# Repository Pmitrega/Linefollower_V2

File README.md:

# Linefollower_V2
Continuation of Linefollower project on new board

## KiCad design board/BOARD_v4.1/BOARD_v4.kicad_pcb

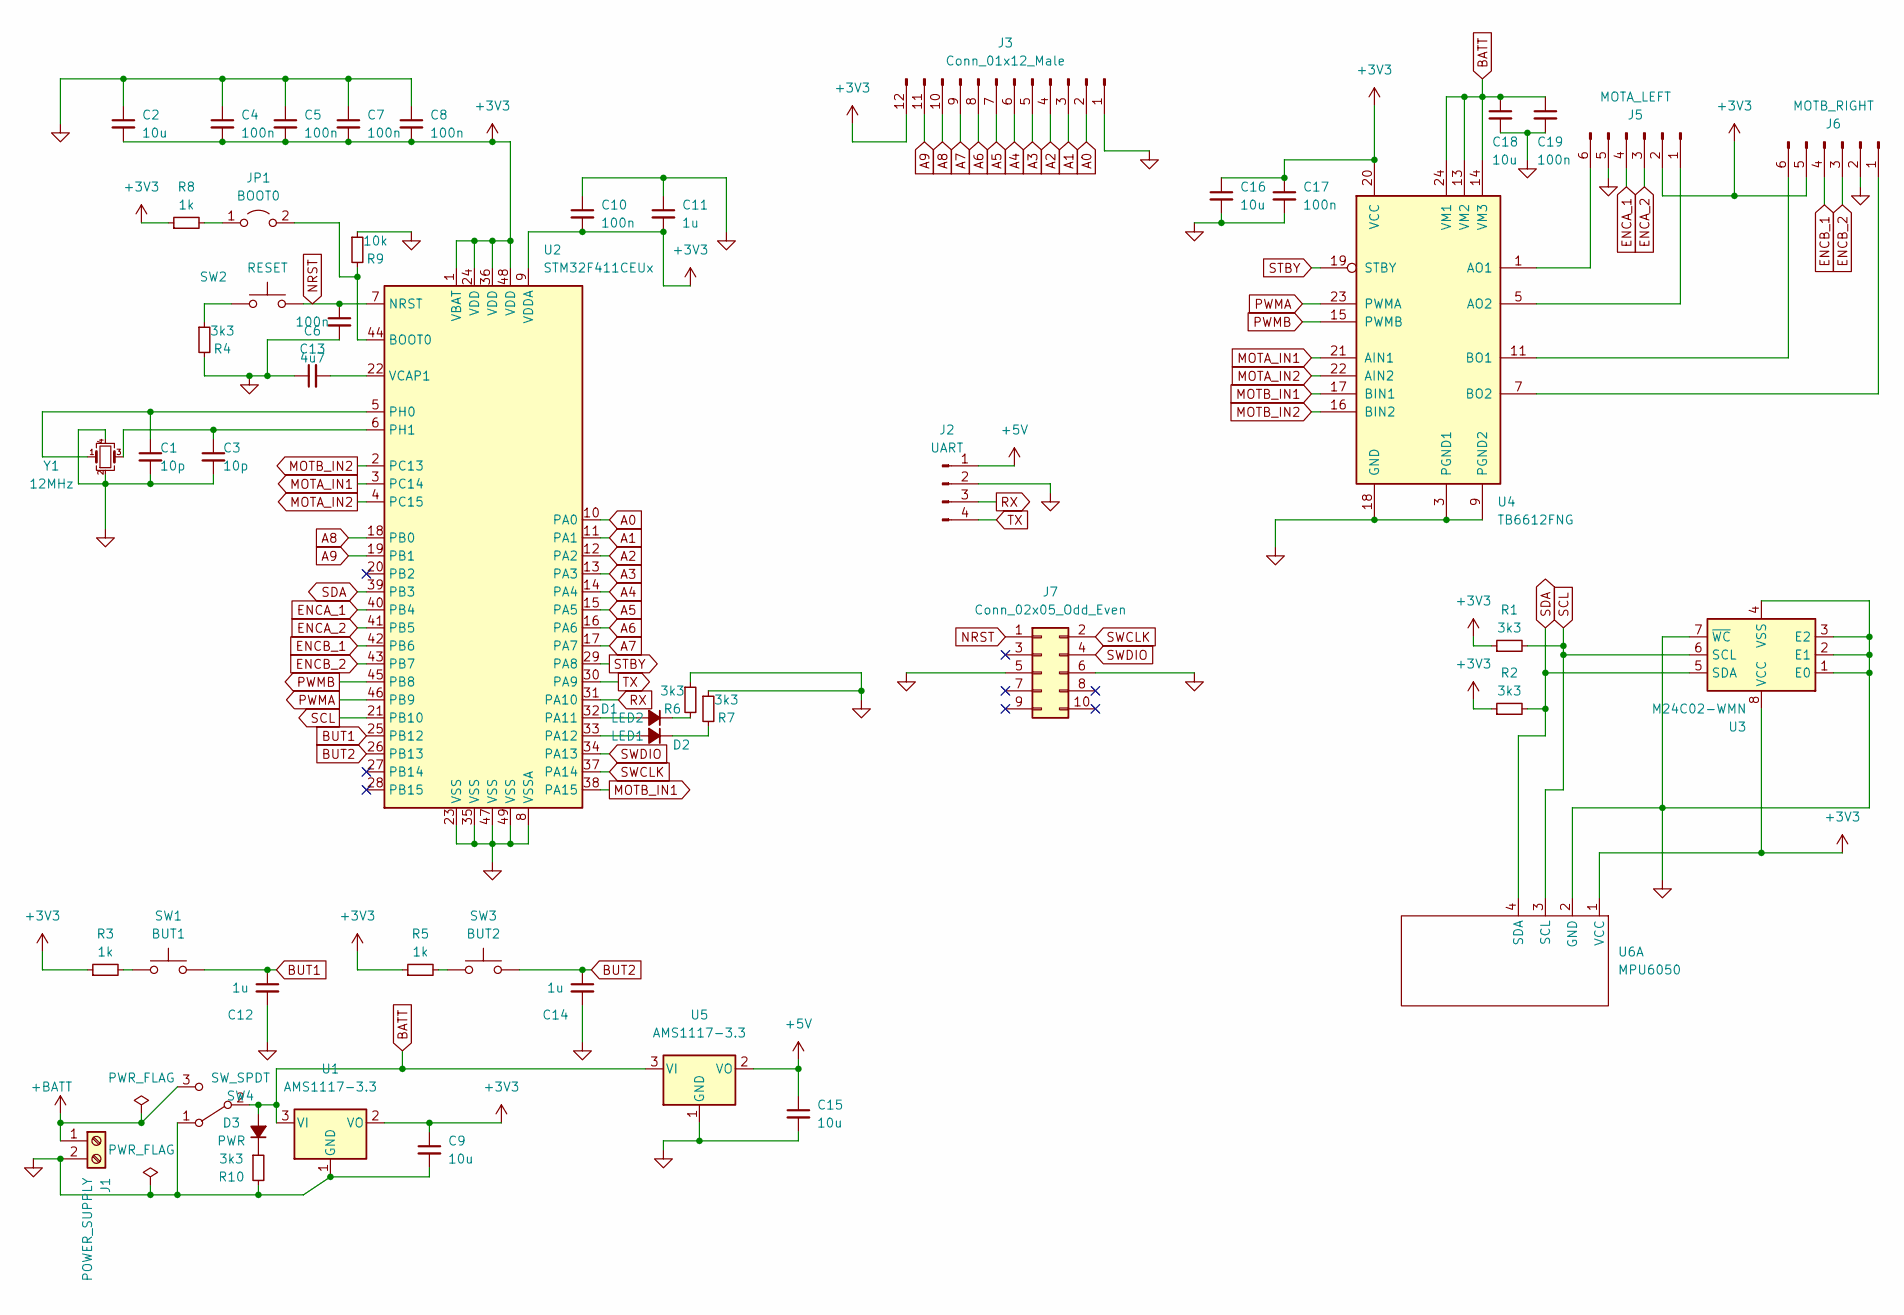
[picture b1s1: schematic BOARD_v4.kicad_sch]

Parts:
C1, C3: 10p; C_0603_1608Metric_Pad1.08x0.95mm_HandSolder
C2, C9, C15, C16, C18: 10u; C_0805_2012Metric_Pad1.18x1.45mm_HandSolder
C4, C5, C7, C8, C10, C13, C17, C19: 100n; C_0603_1608Metric_Pad1.08x0.95mm_HandSolder
C6: 4u7; C_0603_1608Metric_Pad1.08x0.95mm_HandSolder
C11, C12, C14: 1u; C_0603_1608Metric_Pad1.08x0.95mm_HandSolder
D1: LED2; LED_0805_2012Metric_Pad1.15x1.40mm_HandSolder
D2: LED1; LED_0805_2012Metric_Pad1.15x1.40mm_HandSolder
D3: PWR; LED_0805_2012Metric_Pad1.15x1.40mm_HandSolder
J1: POWER_SUPPLY; TerminalBlock_4Ucon_1x02_P3.50mm_Horizontal
J2: UART; PinSocket_1x04_P2.54mm_Vertical
J3: Conn_01x12_Male; Hirose_FH12-12S-0.5SH_1x12-1MP_P0.50mm_Horizontal
J5: MOTA_LEFT; PinSocket_1x06_P2.54mm_Vertical
J6: MOTB_RIGHT; PinSocket_1x06_P2.54mm_Vertical
J7: Conn_02x05_Odd_Even; IDC-Header_2x05_P2.54mm_Vertical
JP1: BOOT0; PinSocket_1x02_P2.54mm_Vertical
R1, R2, R4, R6, R7, R10: 3k3; R_0805_2012Metric_Pad1.20x1.40mm_HandSolder
R3, R5, R8: 1k; R_0805_2012Metric_Pad1.20x1.40mm_HandSolder
R9: 10k; R_0805_2012Metric_Pad1.20x1.40mm_HandSolder
SW1: BUT1; SW_PUSH_6mm
SW2: RESET; SW_PUSH_6mm
SW3: BUT2; SW_PUSH_6mm
SW4: SW_SPDT; SS22T20
U1, U5: AMS1117-3.3; SOT-223-3_TabPin2
U2: STM32F411CEUx; QFN-48-1EP_7x7mm_P0.5mm_EP5.6x5.6mm; LCSC C60420
U3: M24C02-WMN; SOIC-8_3.9x4.9mm_P1.27mm
U4: TB6612FNG; SSOP-24_5.3x8.2mm_P0.65mm; LCSC C88224
U6: MPU6050; MPU6050THT
Y1: 12MHz; Crystal_SMD_3225-4Pin_3.2x2.5mm_HandSoldering

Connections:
+3V3: C2.2, C4.2, C5.2, C7.2, C8.2, C9.1, C10.2, C11.2, C16.1, C17.1, J3.12, J5.2, J6.5, R1.1, R2.1, R3.1, R5.1, R8.1, U1.2 (VO), U2.1 (VBAT), U2.9 (VDDA), U2.24 (VDD), U2.36 (VDD), U2.48 (VDD), U3.8 (VCC), U4.20 (VCC), U6.1 (VCC)
+5V: C15.1, J2.1, U5.2 (VO)
+BATT: J1.1, SW4.3 (C)
A0: J3.2, U2.10 (PA0)
A1: J3.3, U2.11 (PA1)
A2: J3.4, U2.12 (PA2)
A3: J3.5, U2.13 (PA3)
A4: J3.6, U2.14 (PA4)
A5: J3.7, U2.15 (PA5)
A6: J3.8, U2.16 (PA6)
A7: J3.9, U2.17 (PA7)
A8: J3.10, U2.18 (PB0)
A9: J3.11, U2.19 (PB1)
BATT: C18.1, C19.1, D3.2 (A), SW4.2 (B), U1.3 (VI), U4.13 (VM2), U4.14 (VM3), U4.24 (VM1), U5.3 (VI)
BUT1: C12.1, SW1.2, U2.25 (PB12)
BUT2: C14.1, SW3.2, U2.26 (PB13)
ENCA_1: J5.4, U2.40 (PB4)
ENCA_2: J5.3, U2.41 (PB5)
ENCB_1: J6.4, U2.42 (PB6)
ENCB_2: J6.3, U2.43 (PB7)
GND: C1.2, C2.1, C3.2, C4.1, C5.1, C6.1, C7.1, C8.1, C9.2, C10.1, C11.1, C12.2, C13.2, C14.2, C15.2, C16.2, C17.2, C18.2, C19.2, J1.2, J2.2, J3.1, J5.5, J6.2, J7.5, J7.6, R4.2, R6.1, R7.1, R9.1, R10.2, SW4.1 (A), U1.1 (GND), U2.8 (VSSA), U2.23 (VSS), U2.35 (VSS), U2.47 (VSS), U2.49 (VSS), U3.1 (E0), U3.2 (E1), U3.3 (E2), U3.4 (VSS), U3.7 (~WC), U4.3 (PGND1), U4.4 (PGND1), U4.9 (PGND2), U4.10 (PGND2), U4.18 (GND), U5.1 (GND), U6.2 (GND), Y1.2, Y1.4
MOTA_IN1: U2.3 (PC14), U4.21 (AIN1)
MOTA_IN2: U2.4 (PC15), U4.22 (AIN2)
MOTB_IN1: U2.38 (PA15), U4.17 (BIN1)
MOTB_IN2: U2.2 (PC13), U4.16 (BIN2)
NRST: C13.1, J7.1, SW2.2, U2.7 (NRST)
unnamed: C1.1, U2.5 (PH0), Y1.1
unnamed: C3.1, U2.6 (PH1), Y1.3
unnamed: C6.2, U2.22 (VCAP1)
unnamed: D1.1 (K), R6.2
unnamed: D1.2 (A), U2.32 (PA11)
unnamed: D2.1 (K), R7.2
unnamed: D2.2 (A), U2.33 (PA12)
unnamed: D3.1 (K), R10.1
unnamed: J5.1, U4.5 (AO2), U4.6 (AO2)
unnamed: J5.6, U4.1 (AO1), U4.2 (AO1)
unnamed: J6.1, U4.7 (BO2), U4.8 (BO2)
unnamed: J6.6, U4.11 (BO1), U4.12 (BO1)
unnamed: JP1.1 (A), R8.2
unnamed: JP1.2 (B), R9.2, U2.44 (BOOT0)
unnamed: R3.2, SW1.1
unnamed: R4.1, SW2.1
unnamed: R5.2, SW3.1
PWMA: U2.46 (PB9), U4.23 (PWMA)
PWMB: U2.45 (PB8), U4.15 (PWMB)
RX: J2.3, U2.31 (PA10)
SCL: R1.2, U2.21 (PB10), U3.6 (SCL), U6.3 (SCL)
SDA: R2.2, U2.39 (PB3), U3.5 (SDA), U6.4 (SDA)
STBY: U2.29 (PA8), U4.19 (STBY)
SWCLK: J7.2, U2.37 (PA14)
SWDIO: J7.4, U2.34 (PA13)
TX: J2.4, U2.30 (PA9)

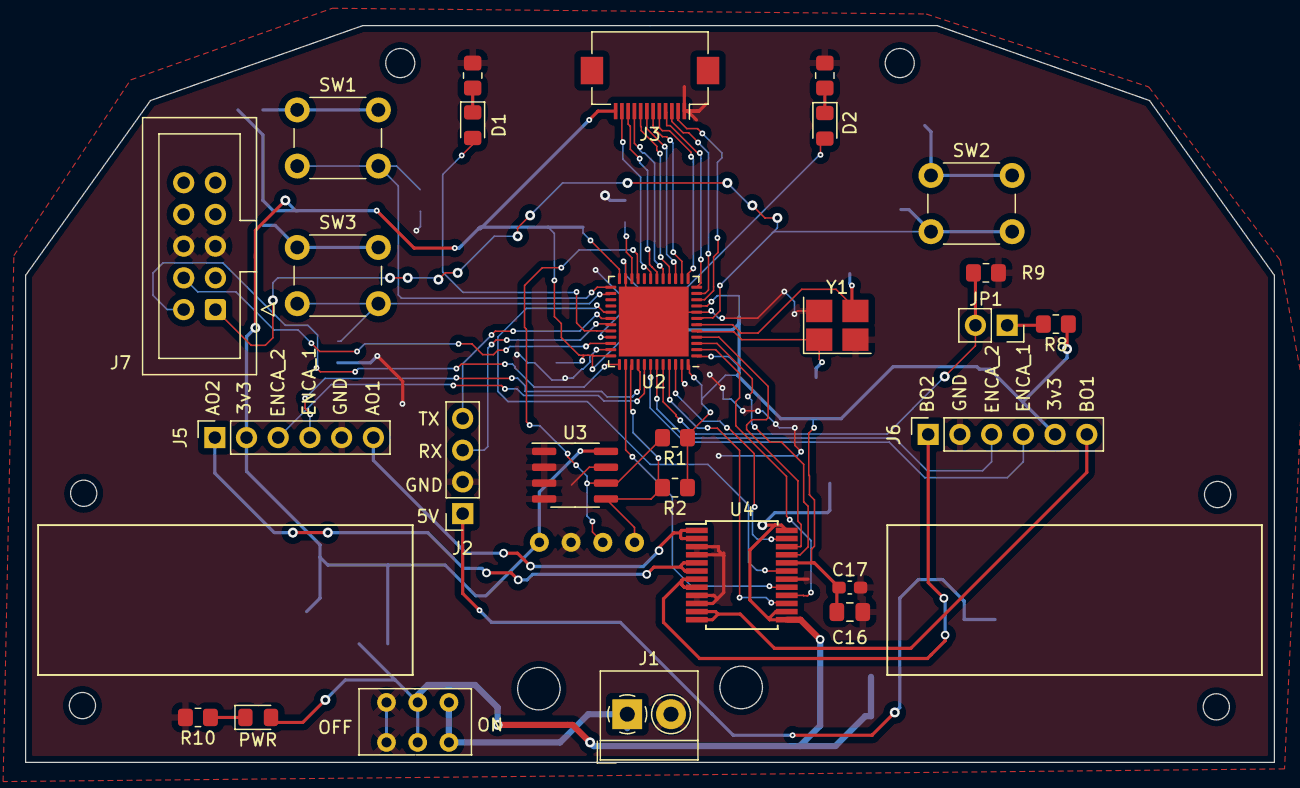
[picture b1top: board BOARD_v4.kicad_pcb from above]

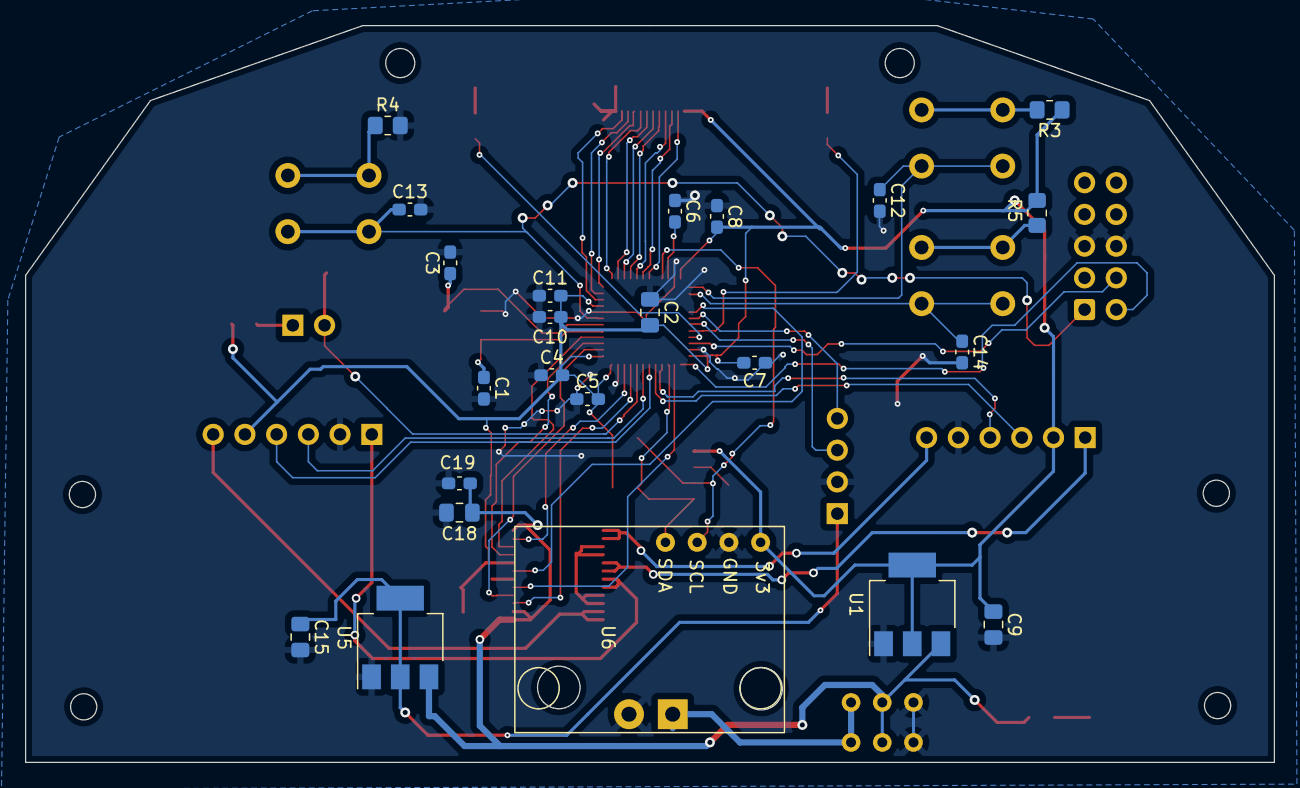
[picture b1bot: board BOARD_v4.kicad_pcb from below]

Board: 2 copper layers, 100.0 x 59.0 mm, 50 parts (23 on the bottom side), 52 nets.

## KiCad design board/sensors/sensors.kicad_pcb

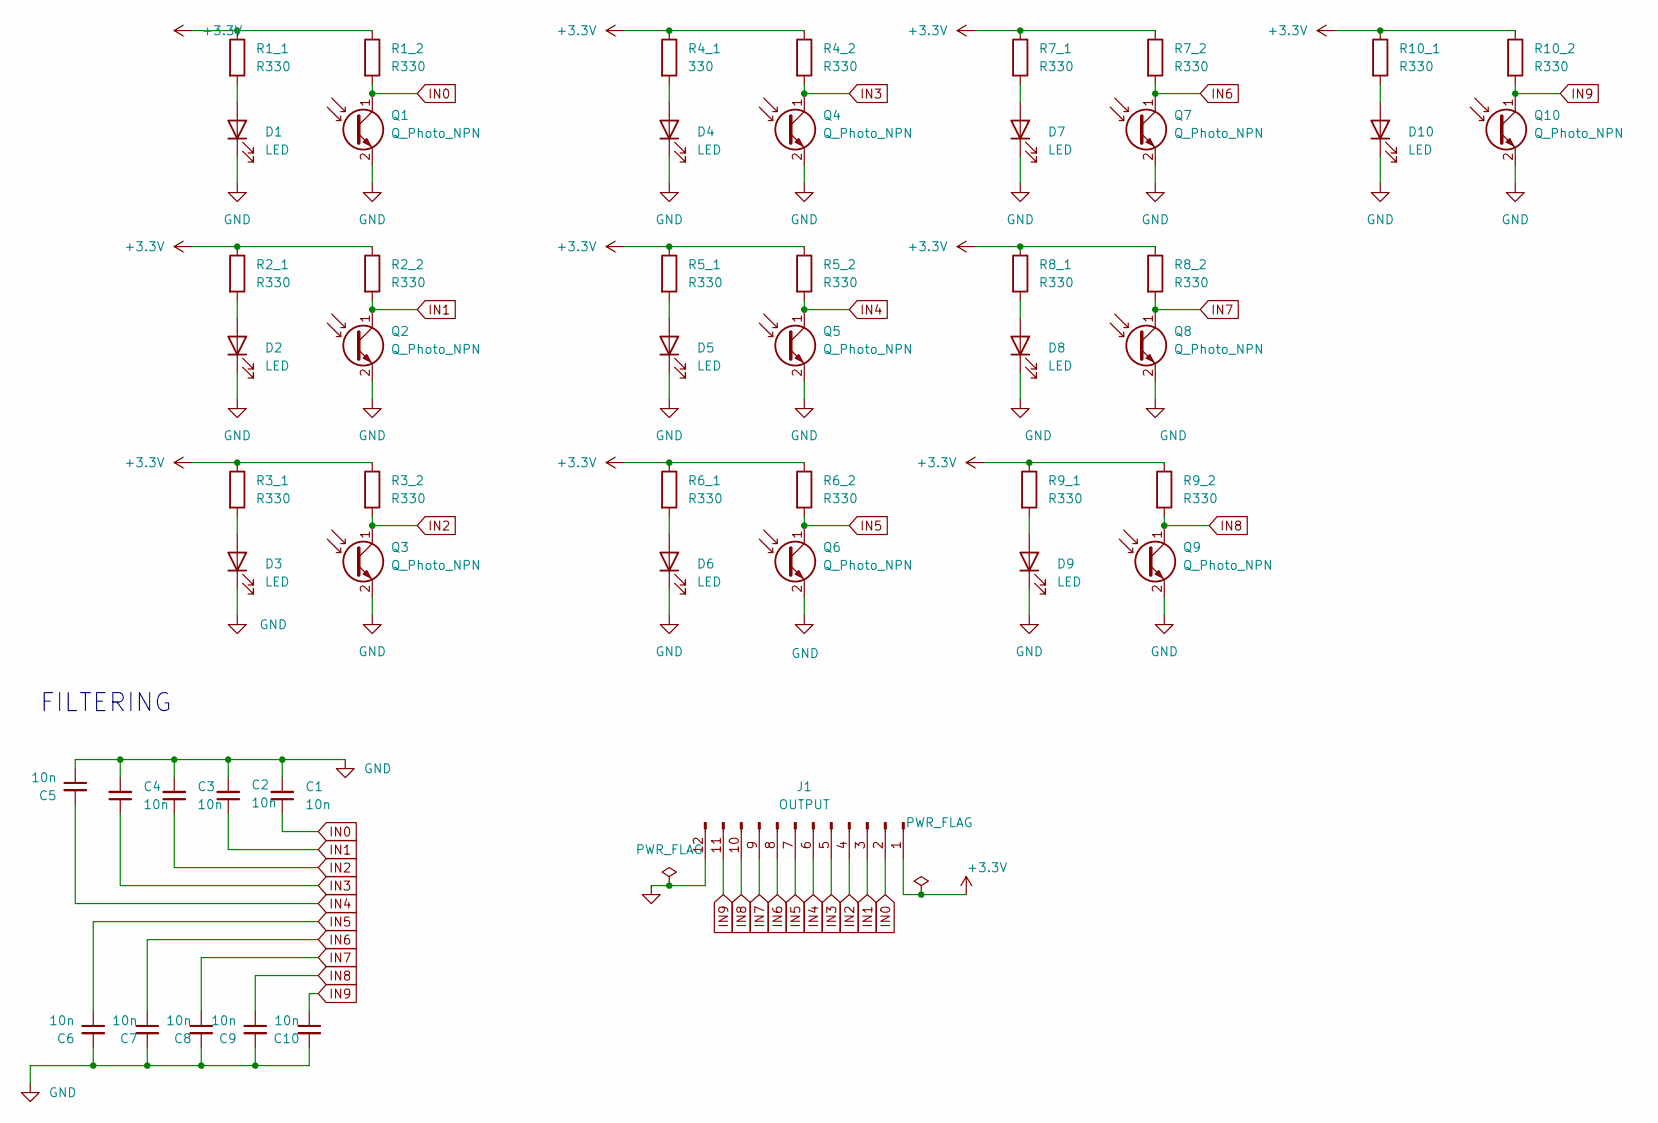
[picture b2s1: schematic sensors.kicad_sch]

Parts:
C1, C2, C3, C4, C5, C6, C7, C8, C9, C10: 10n; C_0805_2012Metric_Pad1.18x1.45mm_HandSolder
D1, D2, D3, D4, D5, D6, D7, D8, D9, D10: LED; R_0805_2012Metric_Pad1.20x1.40mm_HandSolder
J1: OUTPUT; Hirose_FH12-12S-0.5SH_1x12-1MP_P0.50mm_Horizontal
Q1, Q2, Q3, Q4, Q5, Q6, Q7, Q8, Q9, Q10: Q_Photo_NPN; LED_0805_2012Metric_Pad1.15x1.40mm_HandSolder
R1_1, R1_2, R2_1, R2_2, R3_1, R3_2, R4_2, R5_1, R5_2, R6_1, R6_2, R7_1, R7_2, R8_1, R8_2, R9_1, R9_2, R10_1, R10_2: R330; R_0805_2012Metric_Pad1.20x1.40mm_HandSolder
R4_1: 330; R_0805_2012Metric_Pad1.20x1.40mm_HandSolder

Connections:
+3.3V: J1.1, R1_1.1, R1_2.1, R2_1.1, R2_2.1, R3_1.1, R3_2.1, R4_1.1, R4_2.1, R5_1.1, R5_2.1, R6_1.1, R6_2.1, R7_1.1, R7_2.1, R8_1.1, R8_2.1, R9_1.1, R9_2.1, R10_1.1, R10_2.1
GND: C1.2, C2.2, C3.2, C4.2, C5.1, C6.2, C7.2, C8.2, C9.2, C10.2, D1.1 (K), D2.1 (K), D3.1 (K), D4.1 (K), D5.1 (K), D6.1 (K), D7.1 (K), D8.1 (K), D9.1 (K), D10.1 (K), J1.12, Q1.2 (E), Q2.2 (E), Q3.2 (E), Q4.2 (E), Q5.2 (E), Q6.2 (E), Q7.2 (E), Q8.2 (E), Q9.2 (E), Q10.2 (E)
IN0: C1.1, J1.2, Q1.1 (C), R1_2.2
IN1: C2.1, J1.3, Q2.1 (C), R2_2.2
IN2: C3.1, J1.4, Q3.1 (C), R3_2.2
IN3: C4.1, J1.5, Q4.1 (C), R4_2.2
IN4: C5.2, J1.6, Q5.1 (C), R5_2.2
IN5: C6.1, J1.7, Q6.1 (C), R6_2.2
IN6: C7.1, J1.8, Q7.1 (C), R7_2.2
IN7: C8.1, J1.9, Q8.1 (C), R8_2.2
IN8: C9.1, J1.10, Q9.1 (C), R9_2.2
IN9: C10.1, J1.11, Q10.1 (C), R10_2.2
unnamed: D1.2 (A), R1_1.2
unnamed: D2.2 (A), R2_1.2
unnamed: D3.2 (A), R3_1.2
unnamed: D4.2 (A), R4_1.2
unnamed: D5.2 (A), R5_1.2
unnamed: D6.2 (A), R6_1.2
unnamed: D7.2 (A), R7_1.2
unnamed: D8.2 (A), R8_1.2
unnamed: D9.2 (A), R9_1.2
unnamed: D10.2 (A), R10_1.2

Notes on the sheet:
FILTERING

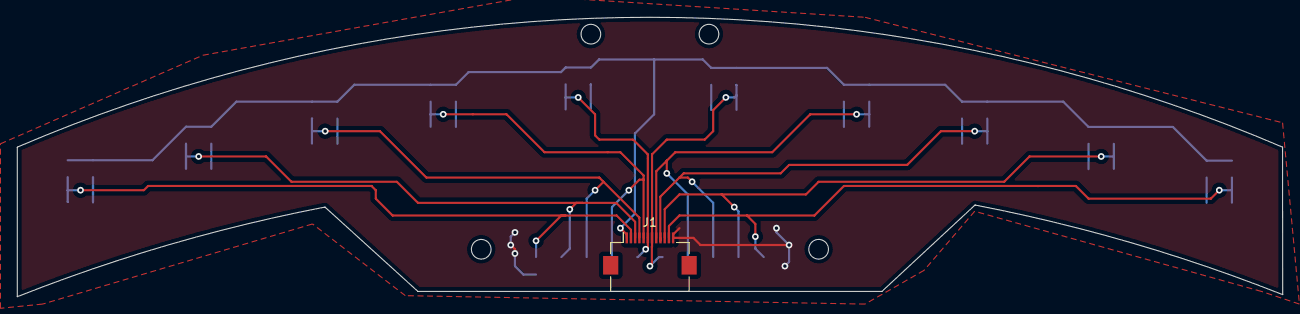
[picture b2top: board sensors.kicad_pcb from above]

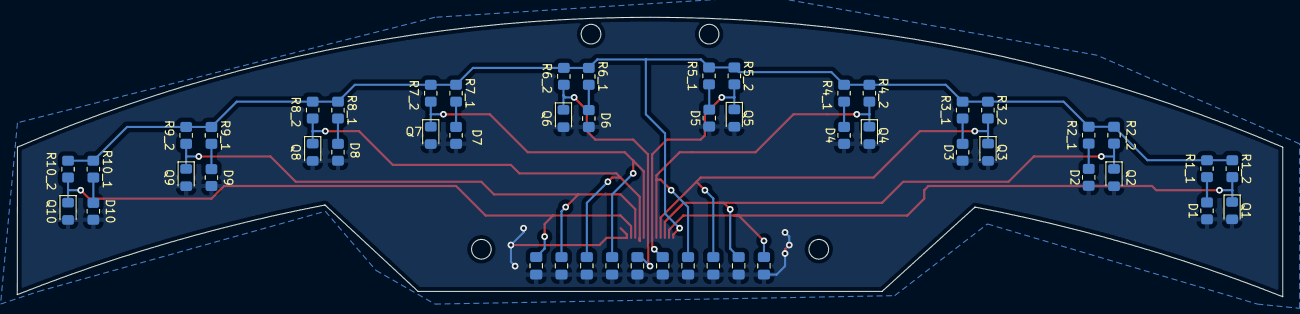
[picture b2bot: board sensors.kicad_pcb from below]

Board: 2 copper layers, 150.0 x 33.1 mm, 51 parts (50 on the bottom side), 22 nets.

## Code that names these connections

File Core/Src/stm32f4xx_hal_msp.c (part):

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    __HAL_RCC_GPIOA_CLK_ENABLE();
    __HAL_RCC_GPIOB_CLK_ENABLE();
    /**ADC1 GPIO Configuration
    PA0-WKUP     ------> ADC1_IN0
    PA1     ------> ADC1_IN1
    PA2     ------> ADC1_IN2
    PA3     ------> ADC1_IN3
    PA4     ------> ADC1_IN4
    PA5     ------> ADC1_IN5
    PA6     ------> ADC1_IN6
    PA7     ------> ADC1_IN7
    PB0     ------> ADC1_IN8
    PB1     ------> ADC1_IN9
    */
    GPIO_InitStruct.Pin = GPIO_PIN_0|GPIO_PIN_1|GPIO_PIN_2|GPIO_PIN_3
                          |GPIO_PIN_4|GPIO_PIN_5|GPIO_PIN_6|GPIO_PIN_7;
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    __HAL_RCC_ADC1_CLK_DISABLE();

    /**ADC1 GPIO Configuration
    PA0-WKUP     ------> ADC1_IN0
    PA1     ------> ADC1_IN1
    PA2     ------> ADC1_IN2
    PA3     ------> ADC1_IN3
    PA4     ------> ADC1_IN4
    PA5     ------> ADC1_IN5
    PA6     ------> ADC1_IN6
    PA7     ------> ADC1_IN7
    PB0     ------> ADC1_IN8
    PB1     ------> ADC1_IN9
    */
    HAL_GPIO_DeInit(GPIOA, GPIO_PIN_0|GPIO_PIN_1|GPIO_PIN_2|GPIO_PIN_3
                          |GPIO_PIN_4|GPIO_PIN_5|GPIO_PIN_6|GPIO_PIN_7);
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
    __HAL_RCC_GPIOB_CLK_ENABLE();
    /**I2C2 GPIO Configuration
    PB10     ------> I2C2_SCL
    PB3     ------> I2C2_SDA
    */
    GPIO_InitStruct.Pin = GPIO_PIN_10;
    GPIO_InitStruct.Mode = GPIO_MODE_AF_OD;
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    __HAL_RCC_I2C2_CLK_DISABLE();

    /**I2C2 GPIO Configuration
    PB10     ------> I2C2_SCL
    PB3     ------> I2C2_SDA
    */
    HAL_GPIO_DeInit(GPIOB, GPIO_PIN_10);

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
    __HAL_RCC_GPIOB_CLK_ENABLE();
    /**TIM3 GPIO Configuration
    PB4     ------> TIM3_CH1
    PB5     ------> TIM3_CH2
    */
    GPIO_InitStruct.Pin = ENCA_1_Pin|ENCA_2_Pin;
    GPIO_InitStruct.Mode = GPIO_MODE_AF_PP;
    GPIO_InitStruct.Pull = GPIO_NOPULL;
    GPIO_InitStruct.Speed = GPIO_SPEED_FREQ_LOW;
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
    __HAL_RCC_GPIOB_CLK_ENABLE();
    /**TIM4 GPIO Configuration
    PB6     ------> TIM4_CH1
    PB7     ------> TIM4_CH2
    */
    GPIO_InitStruct.Pin = ENCB_1_Pin|ENCB_2_Pin;
    GPIO_InitStruct.Mode = GPIO_MODE_AF_PP;
    GPIO_InitStruct.Pull = GPIO_NOPULL;
    GPIO_InitStruct.Speed = GPIO_SPEED_FREQ_LOW;
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  /* USER CODE END TIM10_MspPostInit 0 */
    __HAL_RCC_GPIOB_CLK_ENABLE();
    /**TIM10 GPIO Configuration
    PB8     ------> TIM10_CH1
    */
    GPIO_InitStruct.Pin = PWMB_Pin;
    GPIO_InitStruct.Mode = GPIO_MODE_AF_PP;
    GPIO_InitStruct.Pull = GPIO_NOPULL;
    GPIO_InitStruct.Speed = GPIO_SPEED_FREQ_LOW;
    GPIO_InitStruct.Alternate = GPIO_AF3_TIM10;
    HAL_GPIO_Init(PWMB_GPIO_Port, &GPIO_InitStruct);

  /* USER CODE BEGIN TIM10_MspPostInit 1 */

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
    __HAL_RCC_GPIOB_CLK_ENABLE();
    /**TIM11 GPIO Configuration
    PB9     ------> TIM11_CH1
    */
    GPIO_InitStruct.Pin = PWMA_Pin;
    GPIO_InitStruct.Mode = GPIO_MODE_AF_PP;
    GPIO_InitStruct.Pull = GPIO_NOPULL;
    GPIO_InitStruct.Speed = GPIO_SPEED_FREQ_LOW;
    GPIO_InitStruct.Alternate = GPIO_AF3_TIM11;
    HAL_GPIO_Init(PWMA_GPIO_Port, &GPIO_InitStruct);

  /* USER CODE BEGIN TIM11_MspPostInit 1 */

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    __HAL_RCC_TIM3_CLK_DISABLE();

    /**TIM3 GPIO Configuration
    PB4     ------> TIM3_CH1
    PB5     ------> TIM3_CH2
    */
    HAL_GPIO_DeInit(GPIOB, ENCA_1_Pin|ENCA_2_Pin);

  /* USER CODE BEGIN TIM3_MspDeInit 1 */

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    __HAL_RCC_TIM4_CLK_DISABLE();

    /**TIM4 GPIO Configuration
    PB6     ------> TIM4_CH1
    PB7     ------> TIM4_CH2
    */
    HAL_GPIO_DeInit(GPIOB, ENCB_1_Pin|ENCB_2_Pin);

  /* USER CODE BEGIN TIM4_MspDeInit 1 */

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
    __HAL_RCC_GPIOA_CLK_ENABLE();
    /**USART1 GPIO Configuration
    PA9     ------> USART1_TX
    PA10     ------> USART1_RX
    */
    GPIO_InitStruct.Pin = GPIO_PIN_9|GPIO_PIN_10;
    GPIO_InitStruct.Mode = GPIO_MODE_AF_PP;
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    __HAL_RCC_USART1_CLK_DISABLE();

    /**USART1 GPIO Configuration
    PA9     ------> USART1_TX
    PA10     ------> USART1_RX
    */
    HAL_GPIO_DeInit(GPIOA, GPIO_PIN_9|GPIO_PIN_10);

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
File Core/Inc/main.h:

/* USER CODE BEGIN Header */
/**
  ******************************************************************************
  * @file           : main.h
  * @brief          : Header for main.c file.
  *                   This file contains the common defines of the application.
  ******************************************************************************
  * @attention
  *
  * Copyright (c) 2023 STMicroelectronics.
  * All rights reserved.
  *
  * This software is licensed under terms that can be found in the LICENSE file
  * in the root directory of this software component.
  * If no LICENSE file comes with this software, it is provided AS-IS.
  *
  ******************************************************************************
  */
/* USER CODE END Header */

/* Define to prevent recursive inclusion -------------------------------------*/
#ifndef __MAIN_H
#define __MAIN_H

#ifdef __cplusplus
extern "C" {
#endif

/* Includes ------------------------------------------------------------------*/
#include "stm32f4xx_hal.h"

/* Private includes ----------------------------------------------------------*/
/* USER CODE BEGIN Includes */
#include "motors.h"
/* USER CODE END Includes */

/* Exported types ------------------------------------------------------------*/
/* USER CODE BEGIN ET */

/* USER CODE END ET */

/* Exported constants --------------------------------------------------------*/
/* USER CODE BEGIN EC */

/* USER CODE END EC */

/* Exported macro ------------------------------------------------------------*/
/* USER CODE BEGIN EM */

/* USER CODE END EM */

void HAL_TIM_MspPostInit(TIM_HandleTypeDef *htim);

/* Exported functions prototypes ---------------------------------------------*/
void Error_Handler(void);

/* USER CODE BEGIN EFP */

/* USER CODE END EFP */

/* Private defines -----------------------------------------------------------*/
#define B_IN2_Pin GPIO_PIN_13
#define B_IN2_GPIO_Port GPIOC
#define A_IN1_Pin GPIO_PIN_14
#define A_IN1_GPIO_Port GPIOC
#define A_IN2_Pin GPIO_PIN_15
#define A_IN2_GPIO_Port GPIOC
#define BUT1_Pin GPIO_PIN_12
#define BUT1_GPIO_Port GPIOB
#define BUT2_Pin GPIO_PIN_13
#define BUT2_GPIO_Port GPIOB
#define STBY_Pin GPIO_PIN_8
#define STBY_GPIO_Port GPIOA
#define LED2_Pin GPIO_PIN_11
#define LED2_GPIO_Port GPIOA
#define LED1_Pin GPIO_PIN_12
#define LED1_GPIO_Port GPIOA
#define B_IN1_Pin GPIO_PIN_15
#define B_IN1_GPIO_Port GPIOA
#define ENCA_1_Pin GPIO_PIN_4
#define ENCA_1_GPIO_Port GPIOB
#define ENCA_2_Pin GPIO_PIN_5
#define ENCA_2_GPIO_Port GPIOB
#define ENCB_1_Pin GPIO_PIN_6
#define ENCB_1_GPIO_Port GPIOB
#define ENCB_2_Pin GPIO_PIN_7
#define ENCB_2_GPIO_Port GPIOB
#define PWMB_Pin GPIO_PIN_8
#define PWMB_GPIO_Port GPIOB
#define PWMA_Pin GPIO_PIN_9
#define PWMA_GPIO_Port GPIOB

/* USER CODE BEGIN Private defines */

/* USER CODE END Private defines */

#ifdef __cplusplus
}
#endif

#endif /* __MAIN_H */

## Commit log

2023-02-15 Motor PID, EEPROM handling
2023-02-15 git ignore update
2023-02-16 sensor with DMA reading, further eeprom handling, started making uart interface
2023-02-22 added manual control and entering sensor values manually, automatic control is not yet done, waiting for mechanical parts
2023-02-22 added board scheme in pdf
2023-02-24 kalman filter added to motors position and velocity!
2023-03-24 estimation of angle and sensor reading filtering with exponential filter
2023-04-28 created MPU6050 lib with non-interrupt readings, new sensors board was made, line detection code must be updated
